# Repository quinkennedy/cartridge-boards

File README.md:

This repository is designed to hold various schematics, 
PCB layouts, and associated files for game system cartridges

* [gameboy-mbc0](gameboy-mbc0/)
  - A gameboy cartridge with no Memory Bank Controller. Can hold a ROM up to 32KByte.

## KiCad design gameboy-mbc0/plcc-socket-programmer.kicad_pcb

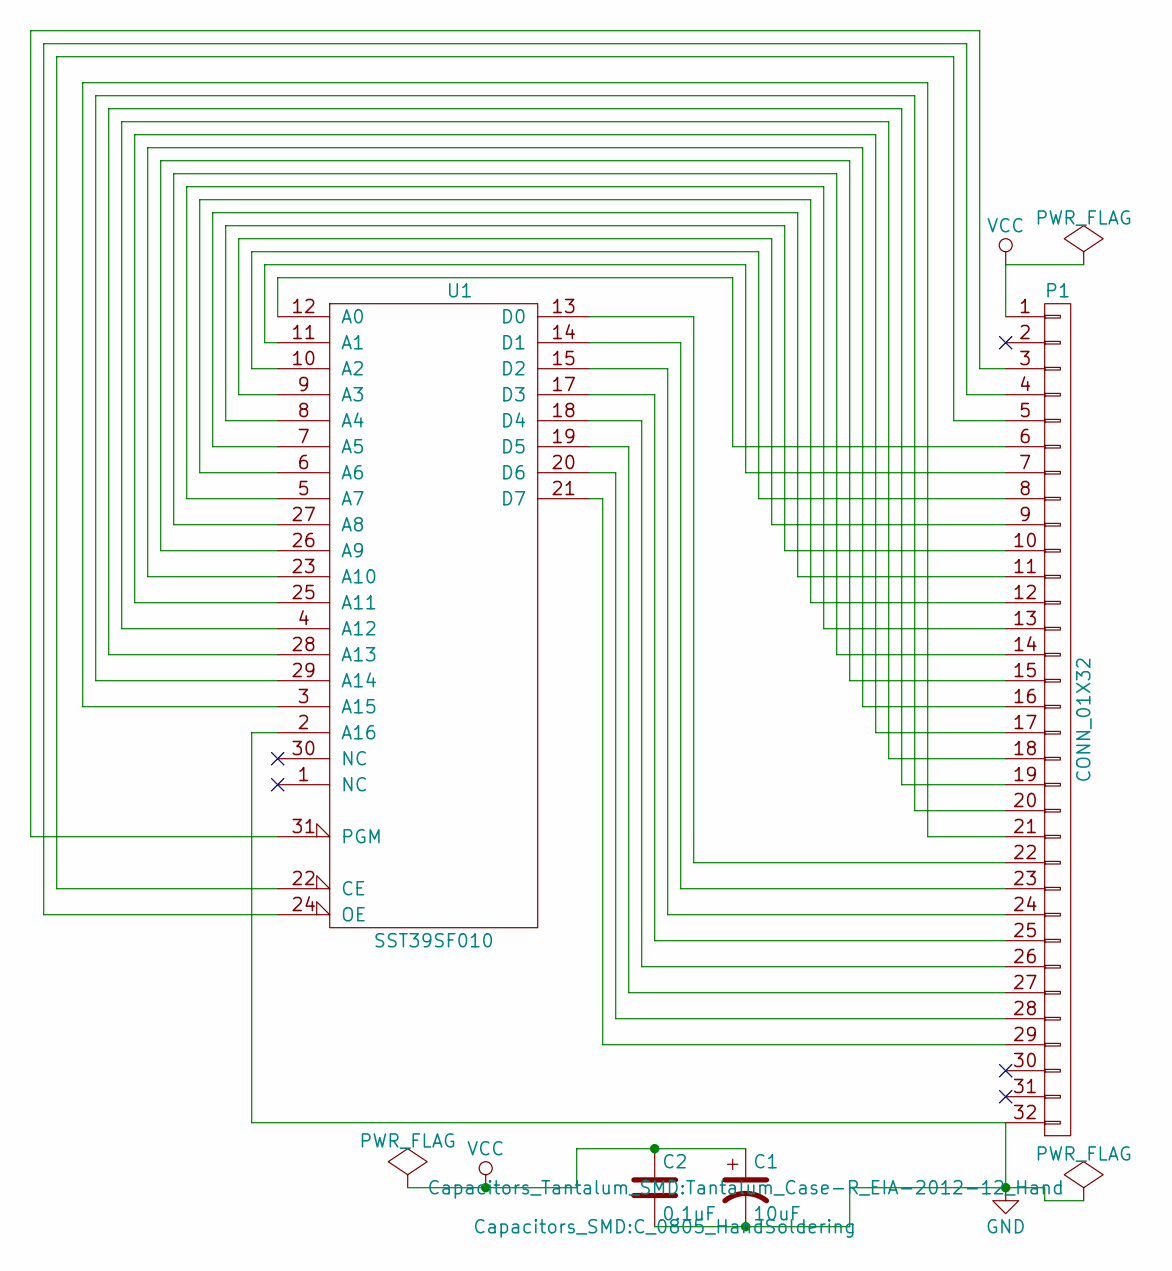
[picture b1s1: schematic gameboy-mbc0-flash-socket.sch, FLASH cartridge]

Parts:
C1: 10uF; Tantalum_Case-R_EIA-2012-12_Hand
C2: 0.1uF; C_0805_HandSoldering
P1: CONN_01X32; Pin_Header_Straight_2x16
U1: SST39SF010; PLCC32

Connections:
GND: C1.2, C2.2, P1.32, U1.2 (A16), U1.16 (GND)
unnamed: P1.3, U1.31 (PGM)
unnamed: P1.4, U1.24 (OE)
unnamed: P1.5, U1.22 (CE)
unnamed: P1.6, U1.12 (A0)
unnamed: P1.7, U1.11 (A1)
unnamed: P1.8, U1.10 (A2)
unnamed: P1.9, U1.9 (A3)
unnamed: P1.10, U1.8 (A4)
unnamed: P1.11, U1.7 (A5)
unnamed: P1.12, U1.6 (A6)
unnamed: P1.13, U1.5 (A7)
unnamed: P1.14, U1.27 (A8)
unnamed: P1.15, U1.26 (A9)
unnamed: P1.16, U1.23 (A10)
unnamed: P1.17, U1.25 (A11)
unnamed: P1.18, U1.4 (A12)
unnamed: P1.19, U1.28 (A13)
unnamed: P1.20, U1.29 (A14)
unnamed: P1.21, U1.3 (A15)
unnamed: P1.22, U1.13 (D0)
unnamed: P1.23, U1.14 (D1)
unnamed: P1.24, U1.15 (D2)
unnamed: P1.25, U1.17 (D3)
unnamed: P1.26, U1.18 (D4)
unnamed: P1.27, U1.19 (D5)
unnamed: P1.28, U1.20 (D6)
unnamed: P1.29, U1.21 (D7)
VCC: C1.1, C2.1, P1.1, U1.32 (VCC)

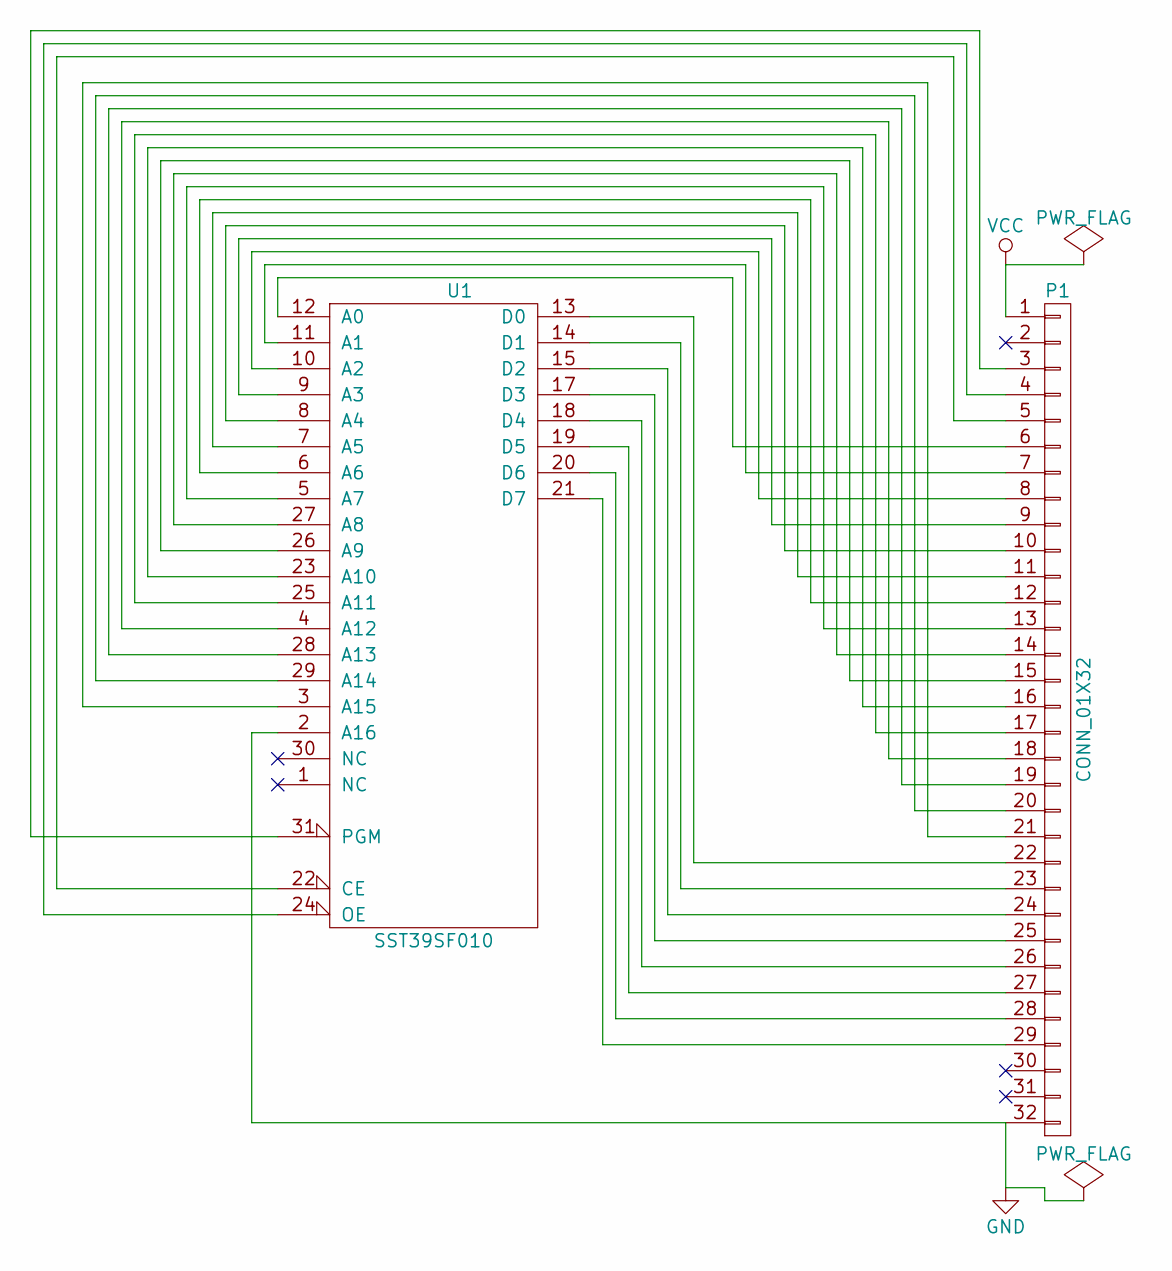
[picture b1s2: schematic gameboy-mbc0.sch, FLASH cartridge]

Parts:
P1: CONN_01X32; GamePak_32
U1: SST39SF010; PLCC-32

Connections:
GND: P1.32, U1.2 (A16), U1.16 (GND); also elsewhere on the board
unnamed: P1.3, U1.31 (PGM)
unnamed: P1.4, U1.24 (OE)
unnamed: P1.5, U1.22 (CE)
unnamed: P1.6, U1.12 (A0)
unnamed: P1.7, U1.11 (A1)
unnamed: P1.8, U1.10 (A2)
unnamed: P1.9, U1.9 (A3)
unnamed: P1.10, U1.8 (A4)
unnamed: P1.11, U1.7 (A5)
unnamed: P1.12, U1.6 (A6)
unnamed: P1.13, U1.5 (A7)
unnamed: P1.14, U1.27 (A8)
unnamed: P1.15, U1.26 (A9)
unnamed: P1.16, U1.23 (A10)
unnamed: P1.17, U1.25 (A11)
unnamed: P1.18, U1.4 (A12)
unnamed: P1.19, U1.28 (A13)
unnamed: P1.20, U1.29 (A14)
unnamed: P1.21, U1.3 (A15)
unnamed: P1.22, U1.13 (D0)
unnamed: P1.23, U1.14 (D1)
unnamed: P1.24, U1.15 (D2)
unnamed: P1.25, U1.17 (D3)
unnamed: P1.26, U1.18 (D4)
unnamed: P1.27, U1.19 (D5)
unnamed: P1.28, U1.20 (D6)
unnamed: P1.29, U1.21 (D7)
VCC: P1.1, U1.32 (VCC); also elsewhere on the board

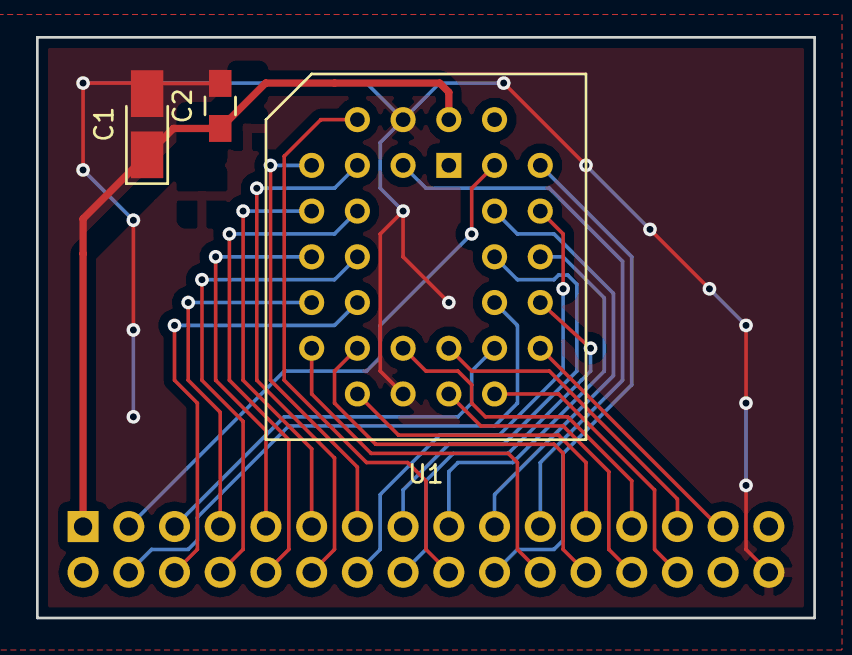
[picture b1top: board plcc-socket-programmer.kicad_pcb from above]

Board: 2 copper layers, 43.2 x 32.3 mm, 4 parts (1 on the bottom side), 29 nets.

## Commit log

2016-11-29 first checkin
2016-11-29 including README
2016-11-29 fixed link
2016-11-29 status changes after Design Rules Check
2016-11-29 including project file for small board
2016-12-14 added keep-out areas to aviod component/cartridge overlap
2016-12-14 moved chip to avoid cartridge case
2016-12-14 successfully rerouted connections and made board smaller
2016-12-14 file updates after closing
2016-12-15 got header/socket pcb started
2016-12-15 wired up data lines
2016-12-15 wired up programmer
2016-12-16 added power smoothing capacitors and board outline
2016-12-16 successful design rules check
2017-10-19 Added in-progress arduino code
    for programming Flash chip
2018-02-22 adding .pro files and pcb updates
